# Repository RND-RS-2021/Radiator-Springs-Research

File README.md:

# Radiator-Springs-Research
**Project for PT. Radiator Springs Indonesia**

Contributor: 
*Nur Imam P,
Husain Asyari,
Maruf Wahyu P*

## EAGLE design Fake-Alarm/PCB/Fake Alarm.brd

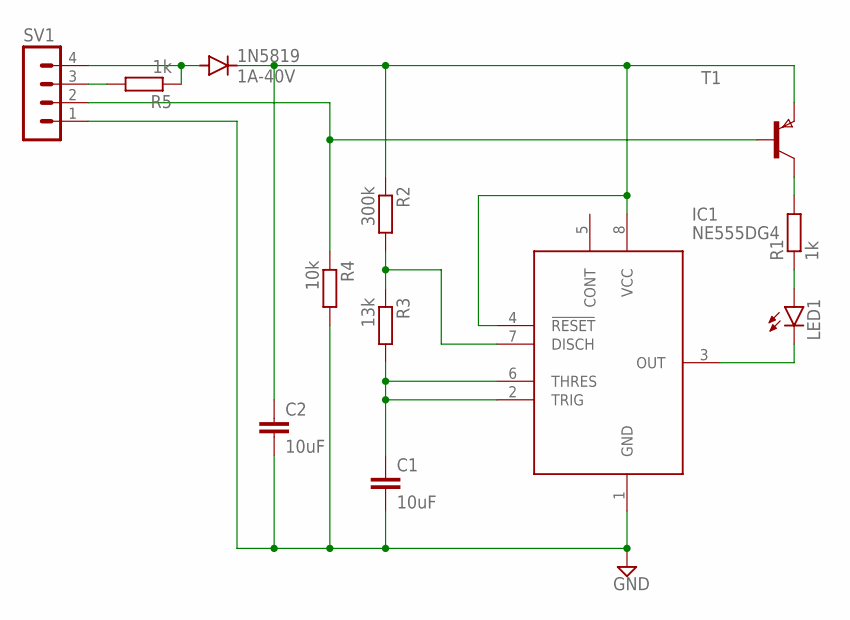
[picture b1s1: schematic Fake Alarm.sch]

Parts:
1N5819: 1A-40V; DO214AC
C1, C2: 10uF; C0805K
IC1: NE555DG4; SOIC127P600X175-8N
LED1: LEDCHIP-LED0805; CHIP-LED0805
R1, R5: 1k; M0805
R2: 300k; M0805
R3: 13k; M0805
R4: 10k; M0805
SV1: MA04-1
T1: PNPSOT23; SOT-23

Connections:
GND: C1.2, C2.2, IC1.1 (GND), R4.2, SV1.1
unnamed: 1N5819.C, C2.1, IC1.4 (!RESET), IC1.8 (VCC), R2.1, T1.2 (E)
unnamed: IC1.3 (OUT), LED1.C
unnamed: LED1.A, R1.1
unnamed: R1.2, T1.1 (C)
unnamed: R4.1, SV1.2, T1.3 (B)
unnamed: IC1.7 (DISCH), R2.2, R3.1
unnamed: C1.1, IC1.2 (TRIG), IC1.6 (THRES), R3.2
unnamed: R5.2, SV1.3
unnamed: 1N5819.A, R5.1, SV1.4

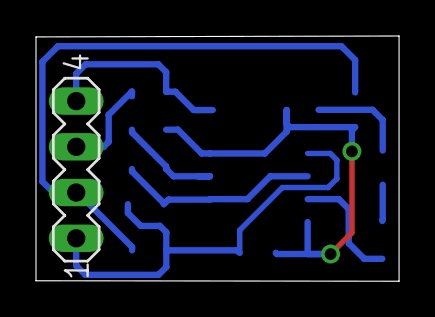
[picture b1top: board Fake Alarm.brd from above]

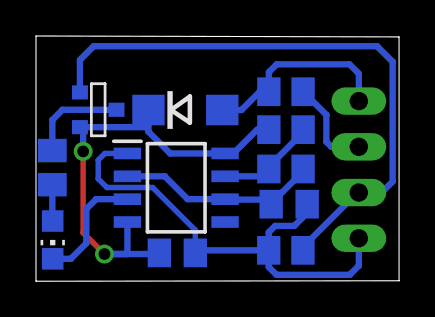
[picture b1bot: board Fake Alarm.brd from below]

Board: 2 copper layers, 20.2 x 13.6 mm, 12 parts (11 on the bottom side), 10 nets.

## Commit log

2021-08-15 Stabilizer Cover and PCB
2021-08-15 Readme Edit
2021-08-15 Fake Alarm PCB submit
2021-08-16 Remove the OLD
2021-08-16 Update Contributor
2021-08-16 Create MIT License
2021-08-16 Photo Profile RnD SPD
2021-08-16 Delete
